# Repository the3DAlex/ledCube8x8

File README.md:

# ledCube8x8
this is old project and i am not shure that here is all complite information.
If you want to create ledcube goto https://github.com/the3DAlex/ledCube_8_16.

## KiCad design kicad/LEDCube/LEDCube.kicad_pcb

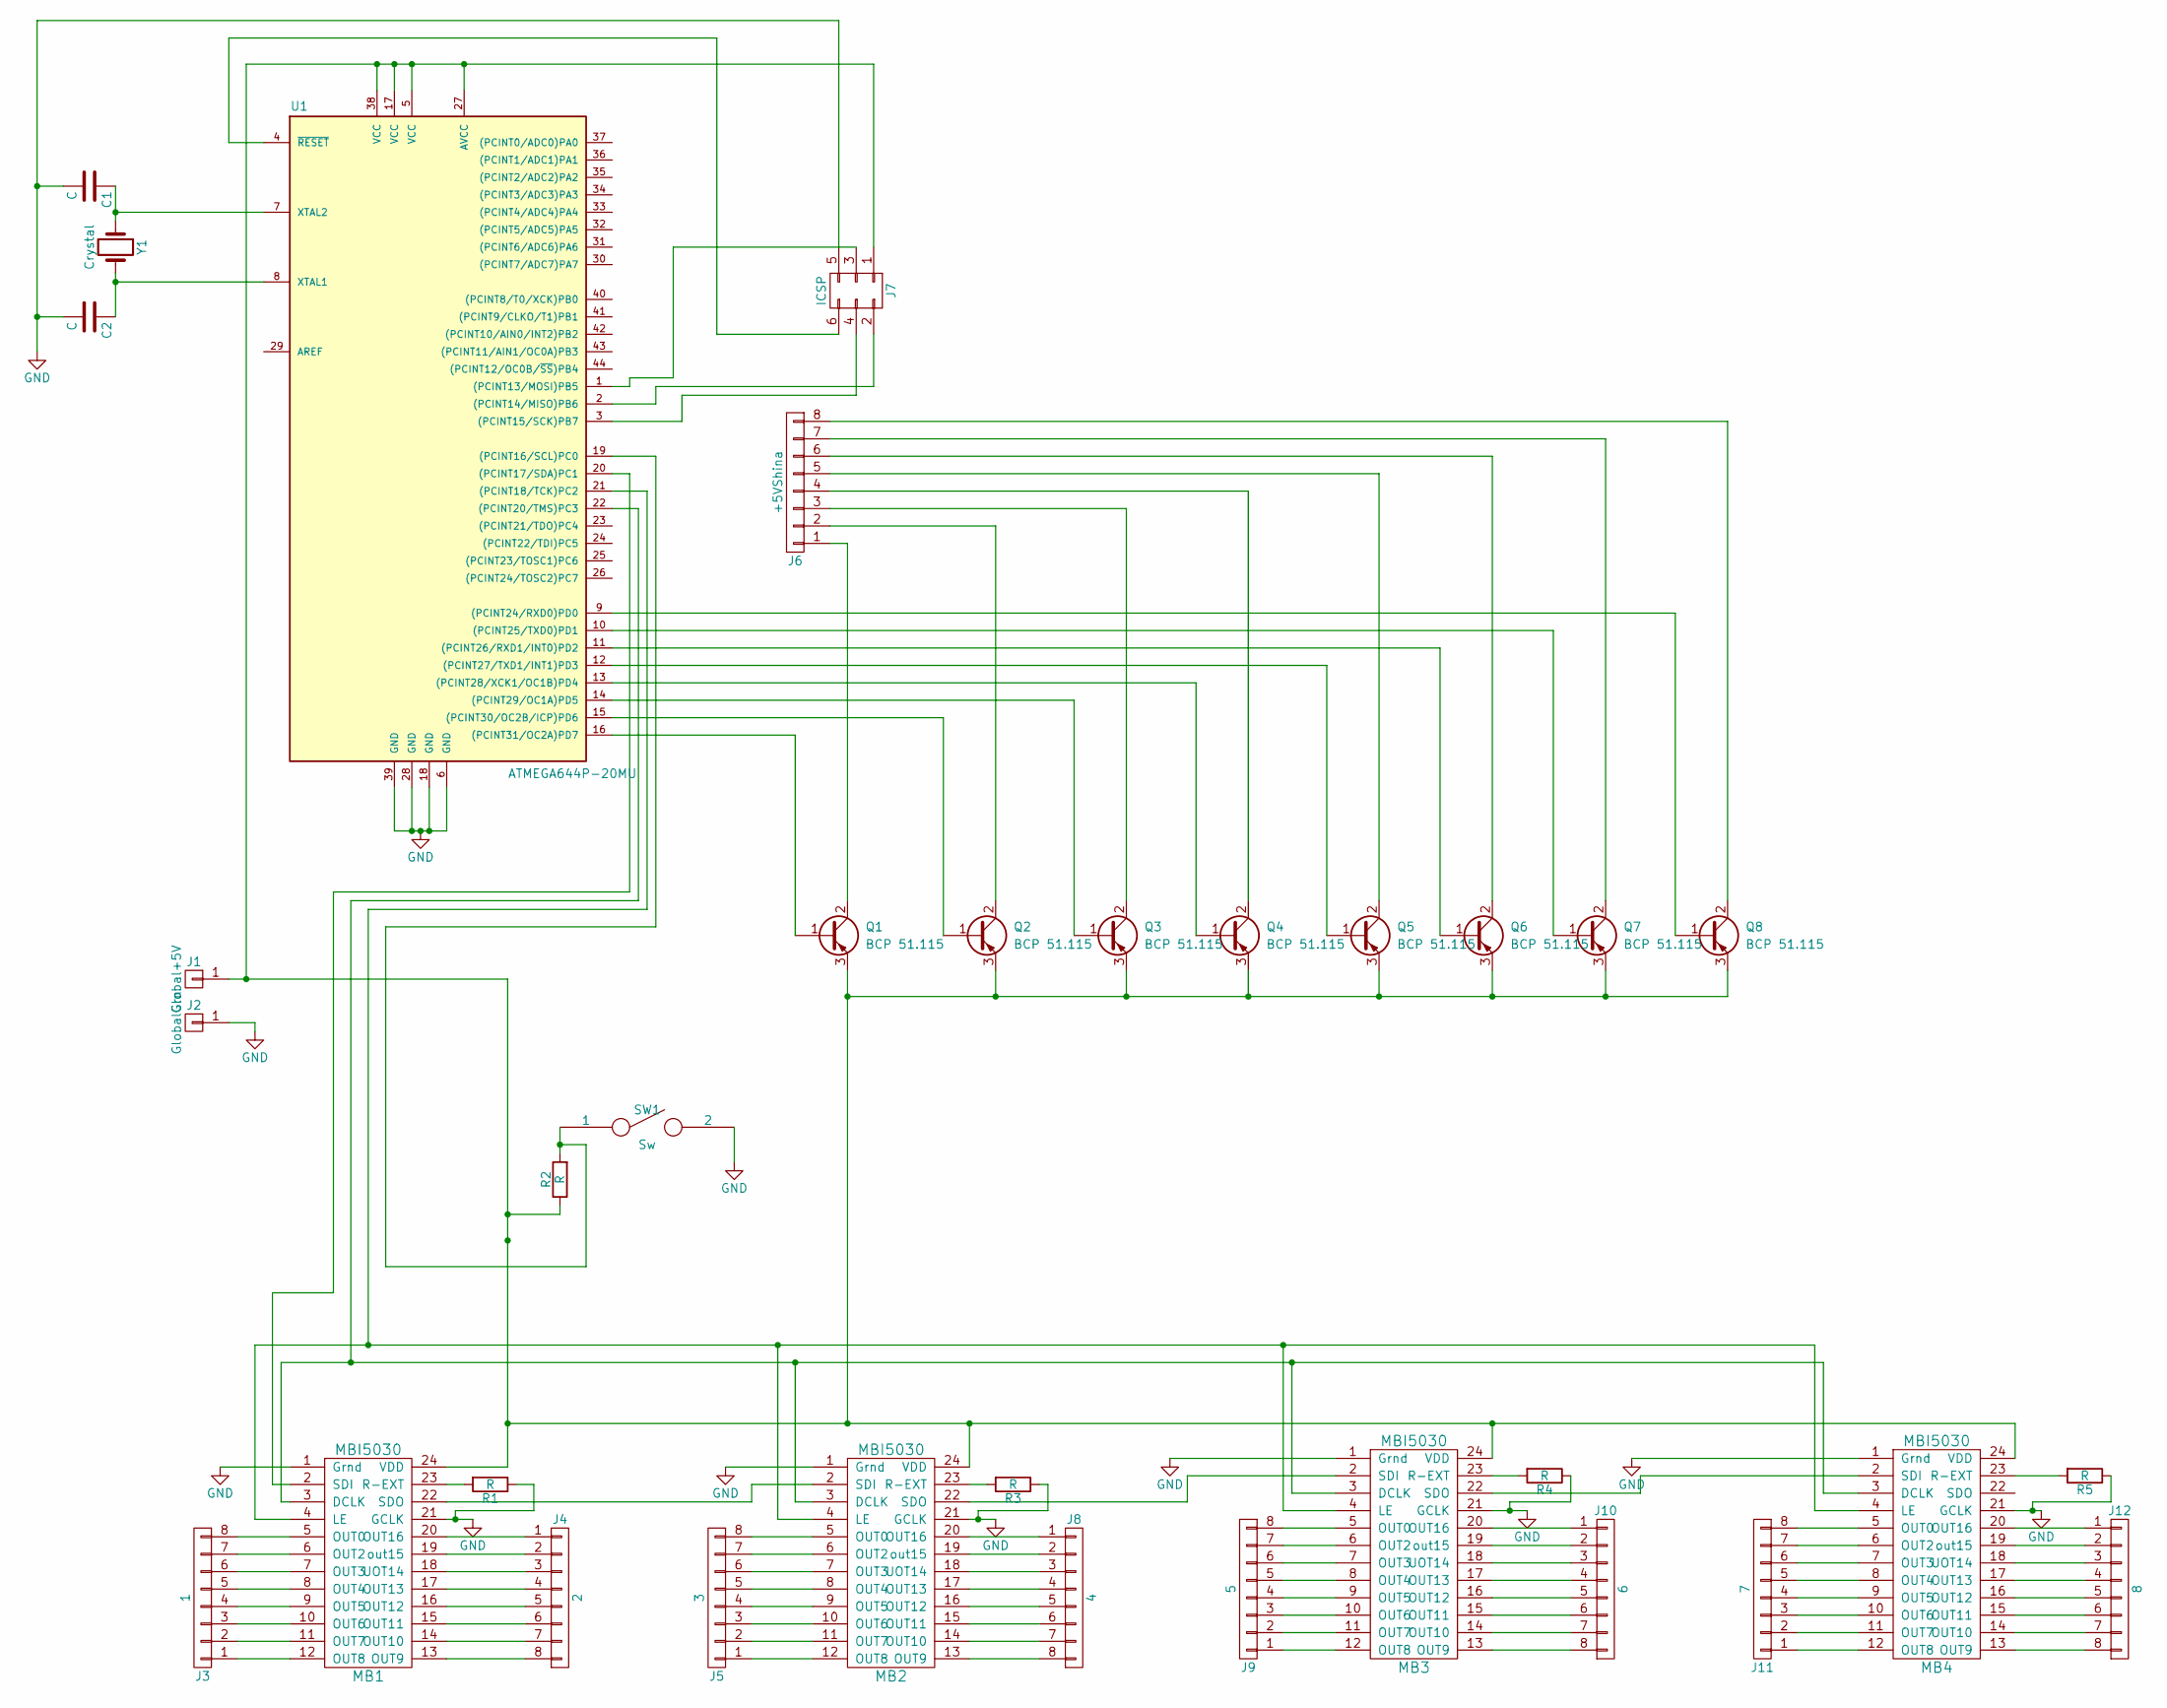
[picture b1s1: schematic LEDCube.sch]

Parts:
C1, C2: C; C_0805
J1: Global+5V; Pin_Header_Straight_1x01_Pitch2.54mm
J2: GlobalGrn; Pin_Header_Straight_1x01_Pitch2.54mm
J3: 1; Pin_Header_Straight_1x08_Pitch1.00mm
J4: 2; Pin_Header_Straight_1x08_Pitch1.00mm
J5: 3; Pin_Header_Straight_1x08_Pitch1.00mm
J6: +5VShina; Pin_Header_Straight_1x08_Pitch1.00mm
J7: ICSP; Pin_Header_Straight_2x03_Pitch2.54mm
J8: 4; Pin_Header_Straight_1x08_Pitch1.00mm
J9: 5; Pin_Header_Straight_1x08_Pitch1.00mm
J10: 6; Pin_Header_Straight_1x08_Pitch1.00mm
J11: 7; Pin_Header_Straight_1x08_Pitch1.00mm
J12: 8; Pin_Header_Straight_1x08_Pitch1.00mm
MB1, MB2, MB3, MB4: MBI5030
Q1, Q2, Q3, Q4, Q5, Q6, Q7, Q8: BCP 51.115; SOT-223
R1, R2, R3, R4, R5: R; R_0805
SW1: Sw; button
U1: ATMEGA644P-20MU; TQFP-44_10x10mm_Pitch0.8mm
Y1: Crystal; Crystal_HC49-U_Vertical

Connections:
GND: C1.2, C2.2, J2.1, J7.5, MB1.1 (Grnd), MB1.21 (GCLK), MB2.1 (Grnd), MB2.21 (GCLK), MB3.1 (Grnd), MB3.21 (GCLK), MB4.1 (Grnd), MB4.21 (GCLK), R1.1, R3.1, R4.1, R5.1, SW1.2, U1.6 (GND), U1.18 (GND), U1.28 (GND), U1.39 (GND)
unnamed: C1.1, U1.7 (XTAL2), Y1.1
unnamed: C2.1, U1.8 (XTAL1), Y1.2
unnamed: J1.1, J7.1, MB1.24 (VDD), MB2.24 (VDD), MB3.24 (VDD), MB4.24 (VDD), Q1.3 (E), Q2.3 (E), Q3.3 (E), Q4.3 (E), Q5.3 (E), Q6.3 (E), Q7.3 (E), Q8.3 (E), R2.1, U1.5 (VCC), U1.17 (VCC), U1.27 (AVCC), U1.38 (VCC)
unnamed: J3.1, MB1.12 (OUT8)
unnamed: J3.2, MB1.11 (OUT7)
unnamed: J3.3, MB1.10 (OUT6)
unnamed: J3.4, MB1.9 (OUT5)
unnamed: J3.5, MB1.8 (OUT4)
unnamed: J3.6, MB1.7 (OUT3)
unnamed: J3.7, MB1.6 (OUT2)
unnamed: J3.8, MB1.5 (OUT0)
unnamed: J4.1, MB1.20 (OUT16)
unnamed: J4.2, MB1.19 (out15)
unnamed: J4.3, MB1.18 (UOT14)
unnamed: J4.4, MB1.17 (OUT13)
unnamed: J4.5, MB1.16 (OUT12)
unnamed: J4.6, MB1.15 (OUT11)
unnamed: J4.7, MB1.14 (OUT10)
unnamed: J4.8, MB1.13 (OUT9)
unnamed: J5.1, MB2.12 (OUT8)
unnamed: J5.2, MB2.11 (OUT7)
unnamed: J5.3, MB2.10 (OUT6)
unnamed: J5.4, MB2.9 (OUT5)
unnamed: J5.5, MB2.8 (OUT4)
unnamed: J5.6, MB2.7 (OUT3)
unnamed: J5.7, MB2.6 (OUT2)
unnamed: J5.8, MB2.5 (OUT0)
unnamed: J6.1, Q1.2 (C)
unnamed: J6.2, Q2.2 (C)
unnamed: J6.3, Q3.2 (C)
unnamed: J6.4, Q4.2 (C)
unnamed: J6.5, Q5.2 (C)
unnamed: J6.6, Q6.2 (C)
unnamed: J6.7, Q7.2 (C)
unnamed: J6.8, Q8.2 (C)
unnamed: J7.2, U1.2 ((PCINT14/MISO)PB6)
unnamed: J7.3, U1.1 ((PCINT13/MOSI)PB5)
unnamed: J7.4, U1.3 ((PCINT15/SCK)PB7)
unnamed: J7.6, U1.4 (~RESET)
unnamed: J8.1, MB2.20 (OUT16)
unnamed: J8.2, MB2.19 (out15)
unnamed: J8.3, MB2.18 (UOT14)
unnamed: J8.4, MB2.17 (OUT13)
unnamed: J8.5, MB2.16 (OUT12)
unnamed: J8.6, MB2.15 (OUT11)
unnamed: J8.7, MB2.14 (OUT10)
unnamed: J8.8, MB2.13 (OUT9)
unnamed: J9.1, MB3.12 (OUT8)
unnamed: J9.2, MB3.11 (OUT7)
unnamed: J9.3, MB3.10 (OUT6)
unnamed: J9.4, MB3.9 (OUT5)
unnamed: J9.5, MB3.8 (OUT4)
unnamed: J9.6, MB3.7 (OUT3)
unnamed: J9.7, MB3.6 (OUT2)
unnamed: J9.8, MB3.5 (OUT0)
unnamed: J10.1, MB3.20 (OUT16)
unnamed: J10.2, MB3.19 (out15)
unnamed: J10.3, MB3.18 (UOT14)
unnamed: J10.4, MB3.17 (OUT13)
unnamed: J10.5, MB3.16 (OUT12)
unnamed: J10.6, MB3.15 (OUT11)
unnamed: J10.7, MB3.14 (OUT10)
unnamed: J10.8, MB3.13 (OUT9)
unnamed: J11.1, MB4.12 (OUT8)
unnamed: J11.2, MB4.11 (OUT7)
unnamed: J11.3, MB4.10 (OUT6)
unnamed: J11.4, MB4.9 (OUT5)
unnamed: J11.5, MB4.8 (OUT4)
unnamed: J11.6, MB4.7 (OUT3)
unnamed: J11.7, MB4.6 (OUT2)
unnamed: J11.8, MB4.5 (OUT0)
unnamed: J12.1, MB4.20 (OUT16)
unnamed: J12.2, MB4.19 (out15)
unnamed: J12.3, MB4.18 (UOT14)
unnamed: J12.4, MB4.17 (OUT13)
unnamed: J12.5, MB4.16 (OUT12)
unnamed: J12.6, MB4.15 (OUT11)
unnamed: J12.7, MB4.14 (OUT10)
unnamed: J12.8, MB4.13 (OUT9)
unnamed: MB1.2 (SDI), U1.20 ((PCINT17/SDA)PC1)
unnamed: MB1.3 (DCLK), MB2.3 (DCLK), MB3.3 (DCLK), MB4.3 (DCLK), U1.22 ((PCINT20/TMS)PC3)
unnamed: MB1.4 (LE), MB2.4 (LE), MB3.4 (LE), MB4.4 (LE), U1.21 ((PCINT18/TCK)PC2)
unnamed: MB1.22 (SDO), MB2.2 (SDI)
unnamed: MB1.23 (R-EXT), R1.2
unnamed: MB2.22 (SDO), MB3.2 (SDI)
unnamed: MB2.23 (R-EXT), R3.2
unnamed: MB3.22 (SDO), MB4.2 (SDI)
unnamed: MB3.23 (R-EXT), R4.2
unnamed: MB4.23 (R-EXT), R5.2
unnamed: Q1.1 (B), U1.16 ((PCINT31/OC2A)PD7)
unnamed: Q2.1 (B), U1.15 ((PCINT30/OC2B/ICP)PD6)
unnamed: Q3.1 (B), U1.14 ((PCINT29/OC1A)PD5)
unnamed: Q4.1 (B), U1.13 ((PCINT28/XCK1/OC1B)PD4)
unnamed: Q5.1 (B), U1.12 ((PCINT27/TXD1/INT1)PD3)
unnamed: Q6.1 (B), U1.11 ((PCINT26/RXD1/INT0)PD2)
unnamed: Q7.1 (B), U1.10 ((PCINT25/TXD0)PD1)
unnamed: Q8.1 (B), U1.9 ((PCINT24/RXD0)PD0)
unnamed: R2.2, SW1.1, U1.19 ((PCINT16/SCL)PC0)

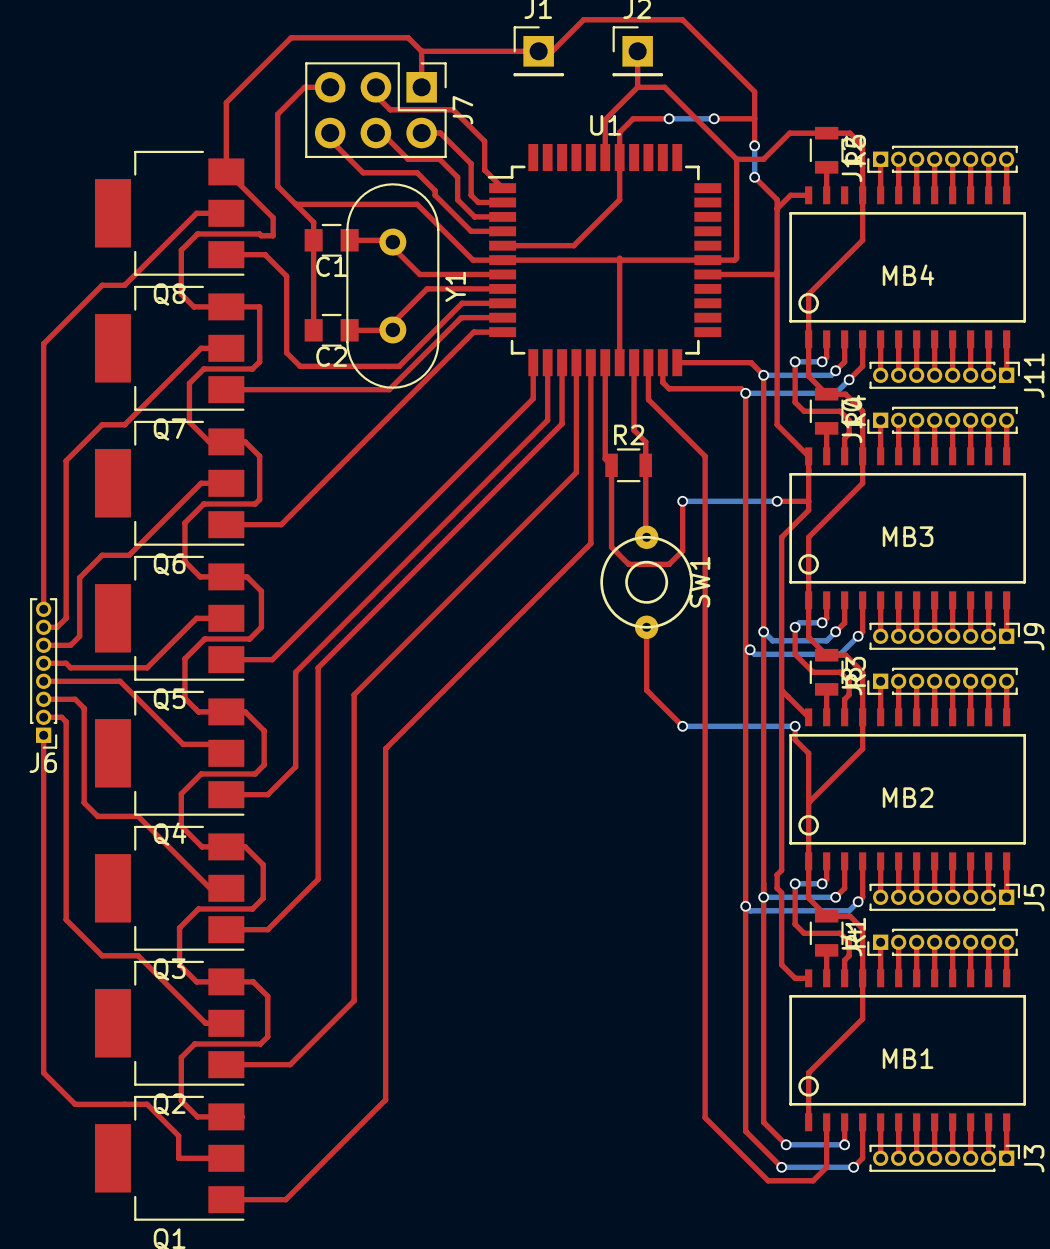
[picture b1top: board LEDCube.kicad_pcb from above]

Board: 2 copper layers, 34 parts (0 on the bottom side), 99 nets.

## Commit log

2021-12-11 old sketch
2021-12-11 kicad proj
2021-12-11 fix mistake
2021-12-12 adaptation from 8x16
